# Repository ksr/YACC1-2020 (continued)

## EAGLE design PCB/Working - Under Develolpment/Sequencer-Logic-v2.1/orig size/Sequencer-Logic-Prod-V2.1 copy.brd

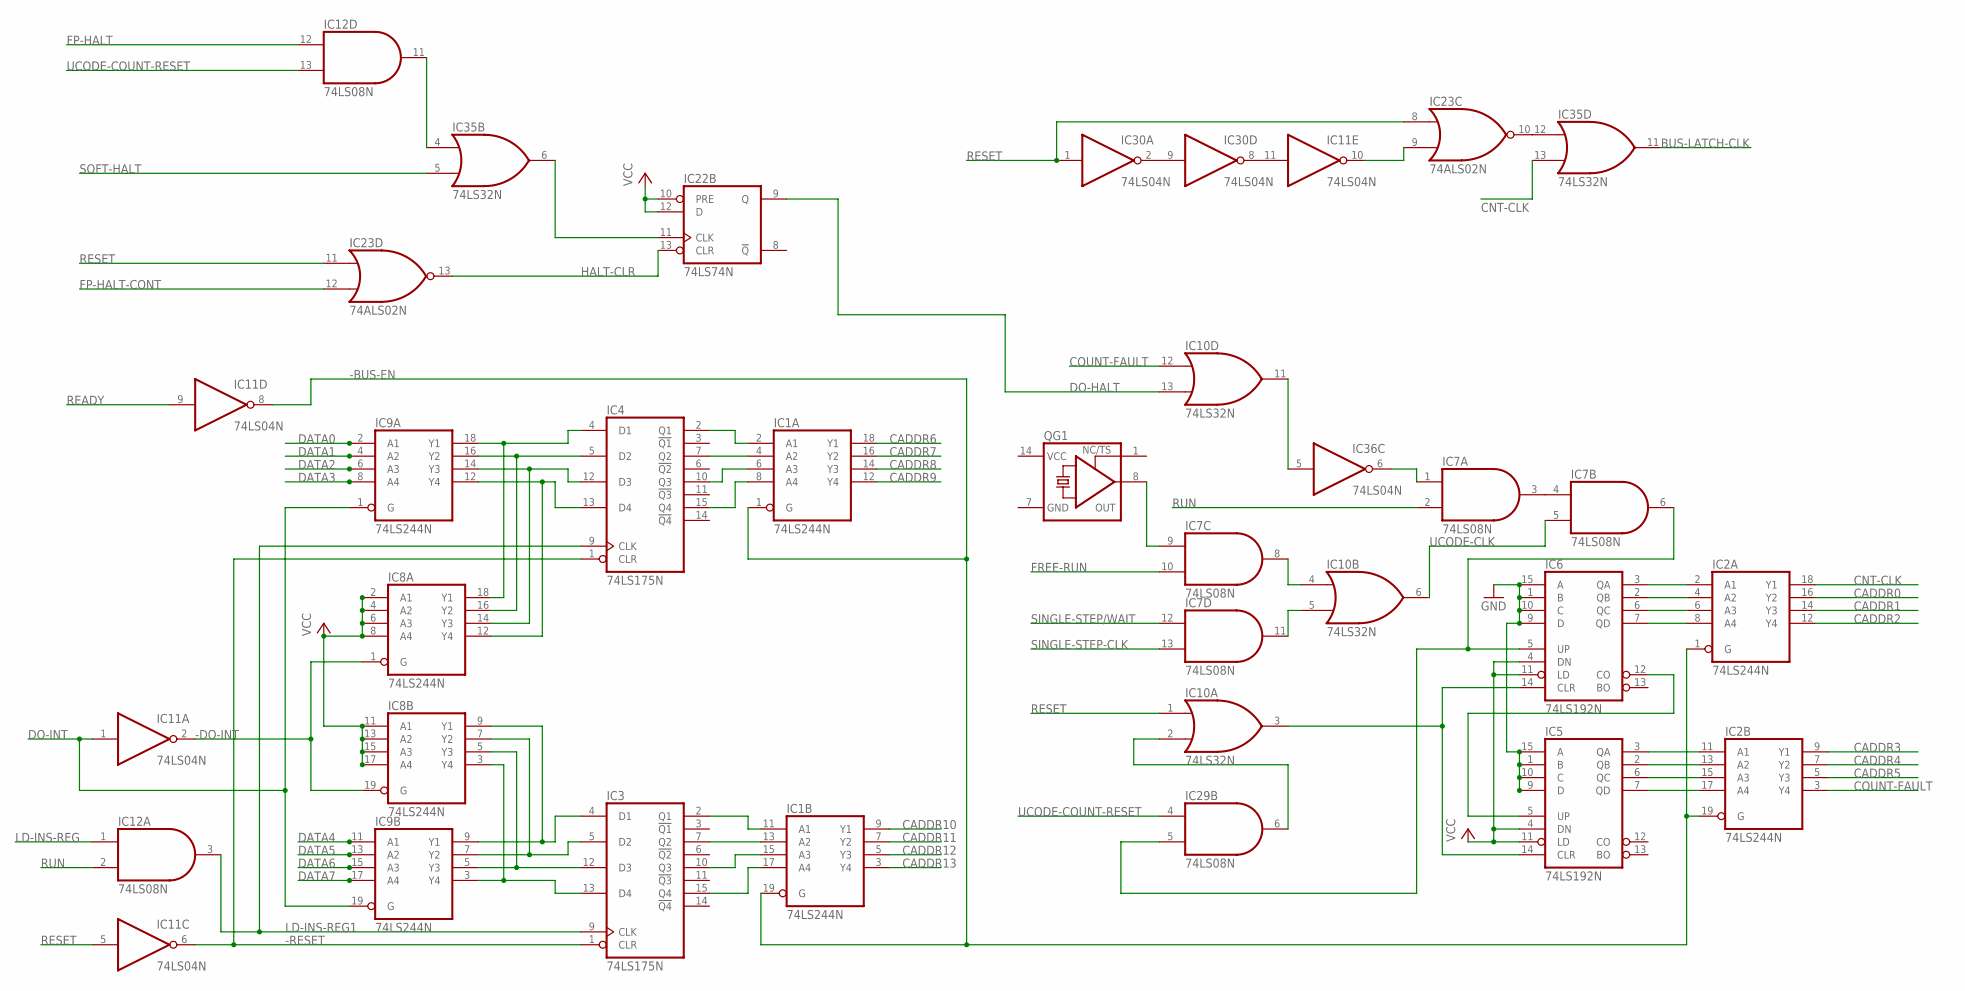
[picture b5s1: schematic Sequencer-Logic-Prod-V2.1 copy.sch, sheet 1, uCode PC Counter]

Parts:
IC1, IC2, IC8, IC9: 74LS244N; DIL20
IC3, IC4: 74LS175N; DIL16
IC5, IC6: 74LS192N; DIL16
IC7, IC12, IC29: 74LS08N; DIL14
IC10, IC35: 74LS32N; DIL14
IC11, IC30, IC36: 74LS04N; DIL14
IC22: 74LS74N; DIL14
IC23: 74ALS02N; DIL14
QG1: XO-14; DIL14S

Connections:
-BUS-EN: IC1.1 (G), IC1.19 (G), IC2.1 (G), IC2.19 (G), IC11.8 (O); also elsewhere on the board
-DO-INT: IC8.1 (G), IC8.19 (G), IC11.2 (O)
-RESET: IC3.1 (CLR), IC4.1 (CLR), IC11.6 (O); also elsewhere on the board
BUS-LATCH-CLK: IC35.11 (O); also elsewhere on the board
CADDR0: IC2.16 (Y2); also elsewhere on the board
CADDR1: IC2.14 (Y3); also elsewhere on the board
CADDR2: IC2.12 (Y4); also elsewhere on the board
CADDR3: IC2.9 (Y1); also elsewhere on the board
CADDR4: IC2.7 (Y2); also elsewhere on the board
CADDR5: IC2.5 (Y3); also elsewhere on the board
CADDR6: IC1.18 (Y1); also elsewhere on the board
CADDR7: IC1.16 (Y2); also elsewhere on the board
CADDR8: IC1.14 (Y3); also elsewhere on the board
CADDR9: IC1.12 (Y4); also elsewhere on the board
CADDR10: IC1.9 (Y1); also elsewhere on the board
CADDR11: IC1.7 (Y2); also elsewhere on the board
CADDR12: IC1.5 (Y3); also elsewhere on the board
CADDR13: IC1.3 (Y4); also elsewhere on the board
CNT-CLK: IC2.18 (Y1), IC35.13 (I1)
COUNT-FAULT: IC2.3 (Y4), IC10.12 (I0)
COUNT-RESET: IC5.14 (CLR), IC6.14 (CLR), IC10.3 (O)
DATA0: IC9.2 (A1); also elsewhere on the board
DATA1: IC9.4 (A2); also elsewhere on the board
DATA2: IC9.6 (A3); also elsewhere on the board
DATA3: IC9.8 (A4); also elsewhere on the board
DATA4: IC9.11 (A1); also elsewhere on the board
DATA5: IC9.13 (A2); also elsewhere on the board
DATA6: IC9.15 (A3); also elsewhere on the board
DATA7: IC9.17 (A4); also elsewhere on the board
DO-HALT: IC10.13 (I1), IC22.9 (Q)
DO-INT: IC9.1 (G), IC9.19 (G), IC11.1 (I); also elsewhere on the board
FP-HALT: IC12.12 (I0); also elsewhere on the board
FP-HALT-CONT: IC23.12 (I1); also elsewhere on the board
FREE-RUN: IC7.10 (I1); also elsewhere on the board
GND: IC1.10 (GND), IC2.10 (GND), IC3.8 (GND), IC4.8 (GND), IC5.1 (B), IC5.8 (GND), IC5.9 (D), IC5.10 (C), IC5.15 (A), IC6.1 (B), IC6.8 (GND), IC6.9 (D), IC6.10 (C), IC6.15 (A), IC7.7 (GND), IC8.10 (GND), IC9.10 (GND), IC10.7 (GND), IC11.7 (GND), IC12.7 (GND), IC22.7 (GND), IC23.7 (GND), IC29.7 (GND), IC30.7 (GND), IC35.7 (GND), IC36.7 (GND), QG1.7 (GND); also elsewhere on the board
HALT-CLR: IC22.13 (CLR), IC23.13 (O)
LD-INS-REG: IC12.1 (I0); also elsewhere on the board
LD-INS-REG1: IC3.9 (CLK), IC4.9 (CLK), IC12.3 (O)
unnamed: IC5.5 (UP), IC6.12 (CO)
unnamed: IC1.2 (A1), IC4.2 (Q1)
unnamed: IC1.4 (A2), IC4.7 (Q2)
unnamed: IC6.5 (UP), IC7.6 (O), IC29.5 (I1)
unnamed: IC4.4 (D1), IC8.18 (Y1), IC9.18 (Y1)
unnamed: IC4.5 (D2), IC8.16 (Y2), IC9.16 (Y2)
unnamed: IC2.2 (A1), IC6.3 (QA)
unnamed: IC2.4 (A2), IC6.2 (QB)
unnamed: IC2.6 (A3), IC6.6 (QC)
unnamed: IC1.6 (A3), IC4.10 (Q3)
unnamed: IC2.8 (A4), IC6.7 (QD)
unnamed: IC2.11 (A1), IC5.3 (QA)
unnamed: IC2.13 (A2), IC5.2 (QB)
unnamed: IC2.15 (A3), IC5.6 (QC)
unnamed: IC2.17 (A4), IC5.7 (QD)
unnamed: IC7.1 (I0), IC36.6 (O)
unnamed: IC4.12 (D3), IC8.14 (Y3), IC9.14 (Y3)
unnamed: IC4.13 (D4), IC8.12 (Y4), IC9.12 (Y4)
unnamed: IC3.4 (D1), IC8.9 (Y1), IC9.9 (Y1)
unnamed: IC3.5 (D2), IC8.7 (Y2), IC9.7 (Y2)
unnamed: IC3.12 (D3), IC8.5 (Y3), IC9.5 (Y3)
unnamed: IC3.13 (D4), IC8.3 (Y4), IC9.3 (Y4)
unnamed: IC1.8 (A4), IC4.15 (Q4)
unnamed: IC10.11 (O), IC36.5 (I)
unnamed: IC7.3 (O), IC7.4 (I0)
unnamed: IC23.10 (O), IC35.12 (I0)
unnamed: IC22.11 (CLK), IC35.6 (O)
unnamed: IC1.11 (A1), IC3.2 (Q1)
unnamed: IC1.13 (A2), IC3.7 (Q2)
unnamed: IC1.15 (A3), IC3.10 (Q3)
unnamed: IC1.17 (A4), IC3.15 (Q4)
unnamed: IC7.11 (O), IC10.5 (I1)
unnamed: IC7.8 (O), IC10.4 (I0)
unnamed: IC7.9 (I0), QG1.8 (OUT)
unnamed: IC11.11 (I), IC30.8 (O)
unnamed: IC30.2 (O), IC30.9 (I)
unnamed: IC11.10 (O), IC23.9 (I1)
unnamed: IC12.11 (O), IC35.4 (I0)
unnamed: IC10.2 (I1), IC29.6 (O)
READY: IC11.9 (I); also elsewhere on the board
RESET: IC10.1 (I0), IC11.5 (I), IC23.8 (I0), IC23.11 (I0), IC30.1 (I); also elsewhere on the board
RUN: IC7.2 (I1), IC12.2 (I1); also elsewhere on the board
SINGLE-STEP-CLK: IC7.13 (I1); also elsewhere on the board
SINGLE-STEP/WAIT: IC7.12 (I0); also elsewhere on the board
SOFT-HALT: IC35.5 (I1); also elsewhere on the board
UCODE-CLK: IC7.5 (I1), IC10.6 (O)
UCODE-COUNT-RESET: IC12.13 (I1), IC29.4 (I0); also elsewhere on the board
VCC: IC1.20 (VCC), IC2.20 (VCC), IC3.16 (VCC), IC4.16 (VCC), IC5.4 (DN), IC5.11 (LD), IC5.16 (VCC), IC6.4 (DN), IC6.11 (LD), IC6.16 (VCC), IC7.14 (VCC), IC8.2 (A1), IC8.4 (A2), IC8.6 (A3), IC8.8 (A4), IC8.11 (A1), IC8.13 (A2), IC8.15 (A3), IC8.17 (A4), IC8.20 (VCC), IC9.20 (VCC), IC10.14 (VCC), IC11.14 (VCC), IC12.14 (VCC), IC22.10 (PRE), IC22.12 (D), IC22.14 (VCC), IC23.14 (VCC), IC29.14 (VCC), IC30.14 (VCC), IC35.14 (VCC), IC36.14 (VCC), QG1.14 (VCC); also elsewhere on the board

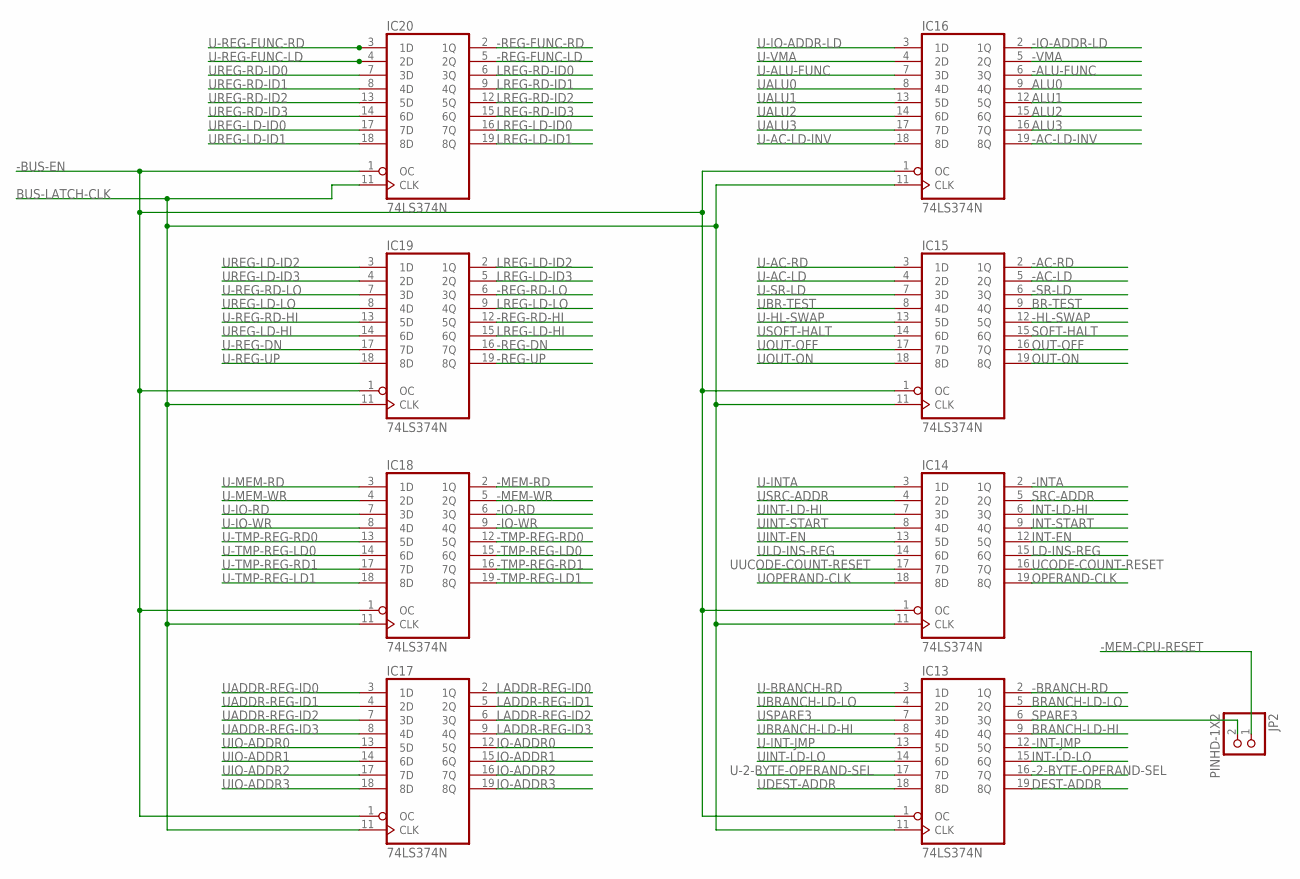
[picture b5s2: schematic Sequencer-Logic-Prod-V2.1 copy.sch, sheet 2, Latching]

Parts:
IC13, IC14, IC15, IC16, IC17, IC18, IC19, IC20: 74LS374N; DIL20
JP2: PINHD-1X2; 1X02

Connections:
-2-BYTE-OPERAND-SEL: IC13.16 (7Q); also elsewhere on the board
-AC-LD: IC15.5 (2Q); also elsewhere on the board
-AC-LD-INV: IC16.19 (8Q); also elsewhere on the board
-AC-RD: IC15.2 (1Q); also elsewhere on the board
-ALU-FUNC: IC16.6 (3Q); also elsewhere on the board
-BRANCH-RD: IC13.2 (1Q); also elsewhere on the board
-BUS-EN: IC13.1 (OC), IC14.1 (OC), IC15.1 (OC), IC16.1 (OC), IC17.1 (OC), IC18.1 (OC), IC19.1 (OC), IC20.1 (OC); also elsewhere on the board
-HL-SWAP: IC15.12 (5Q); also elsewhere on the board
-INT-JMP: IC13.12 (5Q); also elsewhere on the board
-INTA: IC14.2 (1Q); also elsewhere on the board
-IO-ADDR-LD: IC16.2 (1Q); also elsewhere on the board
-IO-RD: IC18.6 (3Q); also elsewhere on the board
-IO-WR: IC18.9 (4Q); also elsewhere on the board
-MEM-CPU-RESET: JP2.1; also elsewhere on the board
-MEM-RD: IC18.2 (1Q); also elsewhere on the board
-MEM-WR: IC18.5 (2Q); also elsewhere on the board
-REG-DN: IC19.16 (7Q); also elsewhere on the board
-REG-FUNC-LD: IC20.5 (2Q); also elsewhere on the board
-REG-FUNC-RD: IC20.2 (1Q); also elsewhere on the board
-REG-RD-HI: IC19.12 (5Q); also elsewhere on the board
-REG-RD-LO: IC19.6 (3Q); also elsewhere on the board
-REG-UP: IC19.19 (8Q); also elsewhere on the board
-SR-LD: IC15.6 (3Q); also elsewhere on the board
-TMP-REG-LD0: IC18.15 (6Q); also elsewhere on the board
-TMP-REG-LD1: IC18.19 (8Q); also elsewhere on the board
-TMP-REG-RD0: IC18.12 (5Q); also elsewhere on the board
-TMP-REG-RD1: IC18.16 (7Q); also elsewhere on the board
-VMA: IC16.5 (2Q); also elsewhere on the board
ALU0: IC16.9 (4Q); also elsewhere on the board
ALU1: IC16.12 (5Q); also elsewhere on the board
ALU2: IC16.15 (6Q); also elsewhere on the board
ALU3: IC16.16 (7Q); also elsewhere on the board
BR-TEST: IC15.9 (4Q); also elsewhere on the board
BRANCH-LD-HI: IC13.9 (4Q); also elsewhere on the board
BRANCH-LD-LO: IC13.5 (2Q); also elsewhere on the board
BUS-LATCH-CLK: IC13.11 (CLK), IC14.11 (CLK), IC15.11 (CLK), IC16.11 (CLK), IC17.11 (CLK), IC18.11 (CLK), IC19.11 (CLK), IC20.11 (CLK); also elsewhere on the board
DEST-ADDR: IC13.19 (8Q); also elsewhere on the board
GND: IC13.10 (GND), IC14.10 (GND), IC15.10 (GND), IC16.10 (GND), IC17.10 (GND), IC18.10 (GND), IC19.10 (GND), IC20.10 (GND); also elsewhere on the board
INT-EN: IC14.12 (5Q); also elsewhere on the board
INT-LD-HI: IC14.6 (3Q); also elsewhere on the board
INT-LD-LO: IC13.15 (6Q); also elsewhere on the board
INT-START: IC14.9 (4Q); also elsewhere on the board
IO-ADDR0: IC17.12 (5Q); also elsewhere on the board
IO-ADDR1: IC17.15 (6Q); also elsewhere on the board
IO-ADDR2: IC17.16 (7Q); also elsewhere on the board
IO-ADDR3: IC17.19 (8Q); also elsewhere on the board
LADDR-REG-ID0: IC17.2 (1Q); also elsewhere on the board
LADDR-REG-ID1: IC17.5 (2Q); also elsewhere on the board
LADDR-REG-ID2: IC17.6 (3Q); also elsewhere on the board
LADDR-REG-ID3: IC17.9 (4Q); also elsewhere on the board
LD-INS-REG: IC14.15 (6Q); also elsewhere on the board
LREG-LD-HI: IC19.15 (6Q); also elsewhere on the board
LREG-LD-ID0: IC20.16 (7Q); also elsewhere on the board
LREG-LD-ID1: IC20.19 (8Q); also elsewhere on the board
LREG-LD-ID2: IC19.2 (1Q); also elsewhere on the board
LREG-LD-ID3: IC19.5 (2Q); also elsewhere on the board
LREG-LD-LO: IC19.9 (4Q); also elsewhere on the board
LREG-RD-ID0: IC20.6 (3Q); also elsewhere on the board
LREG-RD-ID1: IC20.9 (4Q); also elsewhere on the board
LREG-RD-ID2: IC20.12 (5Q); also elsewhere on the board
LREG-RD-ID3: IC20.15 (6Q); also elsewhere on the board
OPERAND-CLK: IC14.19 (8Q); also elsewhere on the board
OUT-OFF: IC15.16 (7Q); also elsewhere on the board
OUT-ON: IC15.19 (8Q); also elsewhere on the board
SOFT-HALT: IC15.15 (6Q); also elsewhere on the board
SPARE3: IC13.6 (3Q), JP2.2
SRC-ADDR: IC14.5 (2Q); also elsewhere on the board
U-2-BYTE-OPERAND-SEL: IC13.17 (7D); also elsewhere on the board
U-AC-LD: IC15.4 (2D); also elsewhere on the board
U-AC-LD-INV: IC16.18 (8D); also elsewhere on the board
U-AC-RD: IC15.3 (1D); also elsewhere on the board
U-ALU-FUNC: IC16.7 (3D); also elsewhere on the board
U-BRANCH-RD: IC13.3 (1D); also elsewhere on the board
U-HL-SWAP: IC15.13 (5D); also elsewhere on the board
U-INT-JMP: IC13.13 (5D); also elsewhere on the board
U-INTA: IC14.3 (1D); also elsewhere on the board
U-IO-ADDR-LD: IC16.3 (1D); also elsewhere on the board
U-IO-RD: IC18.7 (3D); also elsewhere on the board
U-IO-WR: IC18.8 (4D); also elsewhere on the board
U-MEM-RD: IC18.3 (1D); also elsewhere on the board
U-MEM-WR: IC18.4 (2D); also elsewhere on the board
U-REG-DN: IC19.17 (7D); also elsewhere on the board
U-REG-FUNC-LD: IC20.4 (2D); also elsewhere on the board
U-REG-FUNC-RD: IC20.3 (1D); also elsewhere on the board
U-REG-RD-HI: IC19.13 (5D); also elsewhere on the board
U-REG-RD-LO: IC19.7 (3D); also elsewhere on the board
U-REG-UP: IC19.18 (8D); also elsewhere on the board
U-SR-LD: IC15.7 (3D); also elsewhere on the board
U-TMP-REG-LD0: IC18.14 (6D); also elsewhere on the board
U-TMP-REG-LD1: IC18.18 (8D); also elsewhere on the board
U-TMP-REG-RD0: IC18.13 (5D); also elsewhere on the board
U-TMP-REG-RD1: IC18.17 (7D); also elsewhere on the board
U-VMA: IC16.4 (2D); also elsewhere on the board
UADDR-REG-ID0: IC17.3 (1D); also elsewhere on the board
UADDR-REG-ID1: IC17.4 (2D); also elsewhere on the board
UADDR-REG-ID2: IC17.7 (3D); also elsewhere on the board
UADDR-REG-ID3: IC17.8 (4D); also elsewhere on the board
UALU0: IC16.8 (4D); also elsewhere on the board
UALU1: IC16.13 (5D); also elsewhere on the board
UALU2: IC16.14 (6D); also elsewhere on the board
UALU3: IC16.17 (7D); also elsewhere on the board
UBR-TEST: IC15.8 (4D); also elsewhere on the board
UBRANCH-LD-HI: IC13.8 (4D); also elsewhere on the board
UBRANCH-LD-LO: IC13.4 (2D); also elsewhere on the board
UCODE-COUNT-RESET: IC14.16 (7Q); also elsewhere on the board
UDEST-ADDR: IC13.18 (8D); also elsewhere on the board
UINT-EN: IC14.13 (5D); also elsewhere on the board
UINT-LD-HI: IC14.7 (3D); also elsewhere on the board
UINT-LD-LO: IC13.14 (6D); also elsewhere on the board
UINT-START: IC14.8 (4D); also elsewhere on the board
UIO-ADDR0: IC17.13 (5D); also elsewhere on the board
UIO-ADDR1: IC17.14 (6D); also elsewhere on the board
UIO-ADDR2: IC17.17 (7D); also elsewhere on the board
UIO-ADDR3: IC17.18 (8D); also elsewhere on the board
ULD-INS-REG: IC14.14 (6D); also elsewhere on the board
UOPERAND-CLK: IC14.18 (8D); also elsewhere on the board
UOUT-OFF: IC15.17 (7D); also elsewhere on the board
UOUT-ON: IC15.18 (8D); also elsewhere on the board
UREG-LD-HI: IC19.14 (6D); also elsewhere on the board
UREG-LD-ID0: IC20.17 (7D); also elsewhere on the board
UREG-LD-ID1: IC20.18 (8D); also elsewhere on the board
UREG-LD-ID2: IC19.3 (1D); also elsewhere on the board
UREG-LD-ID3: IC19.4 (2D); also elsewhere on the board
UREG-LD-LO: IC19.8 (4D); also elsewhere on the board
UREG-RD-ID0: IC20.7 (3D); also elsewhere on the board
UREG-RD-ID1: IC20.8 (4D); also elsewhere on the board
UREG-RD-ID2: IC20.13 (5D); also elsewhere on the board
UREG-RD-ID3: IC20.14 (6D); also elsewhere on the board
USOFT-HALT: IC15.14 (6D); also elsewhere on the board
USPARE3: IC13.7 (3D); also elsewhere on the board
USRC-ADDR: IC14.4 (2D); also elsewhere on the board
UUCODE-COUNT-RESET: IC14.17 (7D); also elsewhere on the board
VCC: IC13.20 (VCC), IC14.20 (VCC), IC15.20 (VCC), IC16.20 (VCC), IC17.20 (VCC), IC18.20 (VCC), IC19.20 (VCC), IC20.20 (VCC); also elsewhere on the board

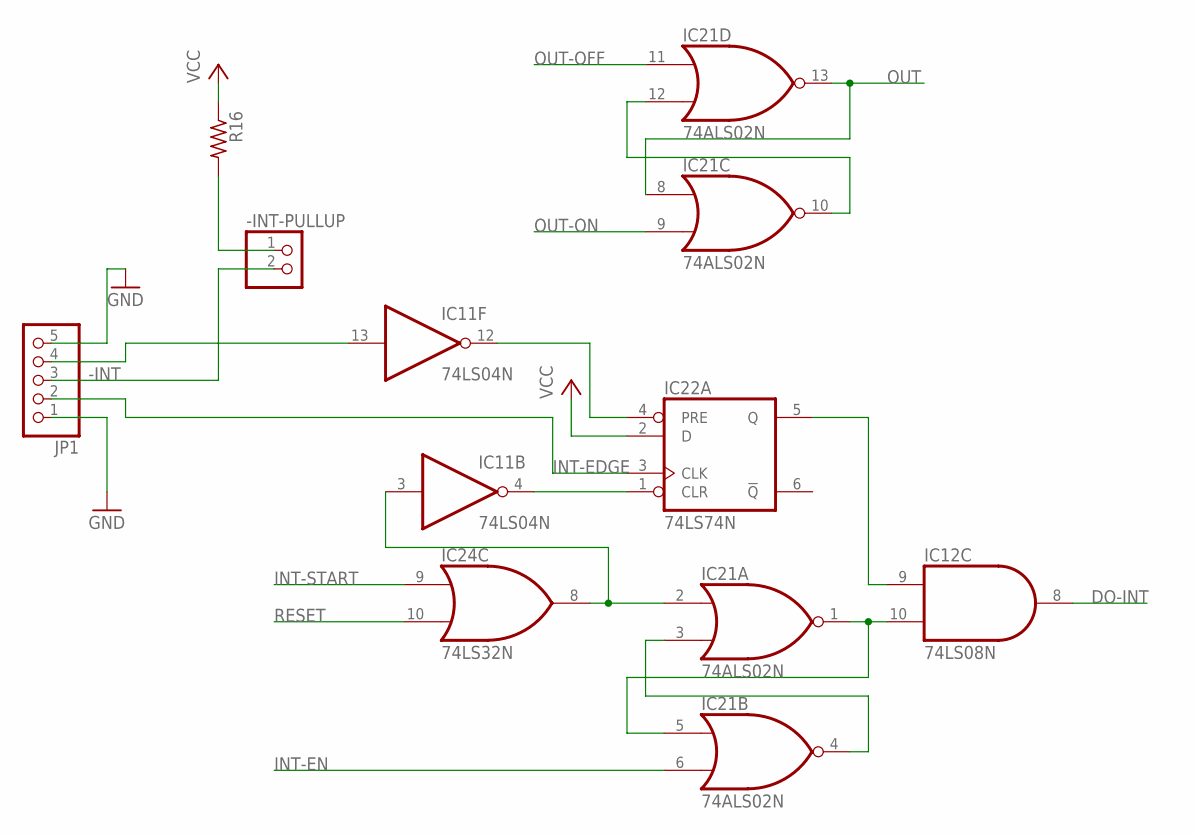
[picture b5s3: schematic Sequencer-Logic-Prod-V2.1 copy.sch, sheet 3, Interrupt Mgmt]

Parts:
-INT-PULLUP: PINHD-1X2; 1X02
IC11: 74LS04N; DIL14
IC12: 74LS08N; DIL14
IC21: 74ALS02N; DIL14
IC22: 74LS74N; DIL14
IC24: 74LS32N; DIL14
JP1: PINHD-1X5; 1X05
R16: 10k; 0207/10

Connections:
-INT: -INT-PULLUP.2, JP1.3; also elsewhere on the board
DO-INT: IC12.8 (O); also elsewhere on the board
GND: IC11.7 (GND), IC12.7 (GND), IC21.7 (GND), IC22.7 (GND), IC24.7 (GND), JP1.1, JP1.5; also elsewhere on the board
INT-EDGE: IC22.3 (CLK), JP1.2
INT-EN: IC21.6 (I1); also elsewhere on the board
INT-START: IC24.9 (I0); also elsewhere on the board
unnamed: IC12.10 (I1), IC21.1 (O), IC21.5 (I0)
unnamed: IC21.3 (I1), IC21.4 (O)
unnamed: IC11.3 (I), IC21.2 (I0), IC24.8 (O)
unnamed: IC12.9 (I0), IC22.5 (Q)
unnamed: IC11.4 (O), IC22.1 (CLR)
unnamed: IC11.12 (O), IC22.4 (PRE)
unnamed: IC11.13 (I), JP1.4
unnamed: IC21.10 (O), IC21.12 (I1)
unnamed: -INT-PULLUP.1, R16.2
OUT: IC21.8 (I0), IC21.13 (O); also elsewhere on the board
OUT-OFF: IC21.11 (I0); also elsewhere on the board
OUT-ON: IC21.9 (I1); also elsewhere on the board
RESET: IC24.10 (I1); also elsewhere on the board
VCC: IC11.14 (VCC), IC12.14 (VCC), IC21.14 (VCC), IC22.2 (D), IC22.14 (VCC), IC24.14 (VCC), R16.1; also elsewhere on the board

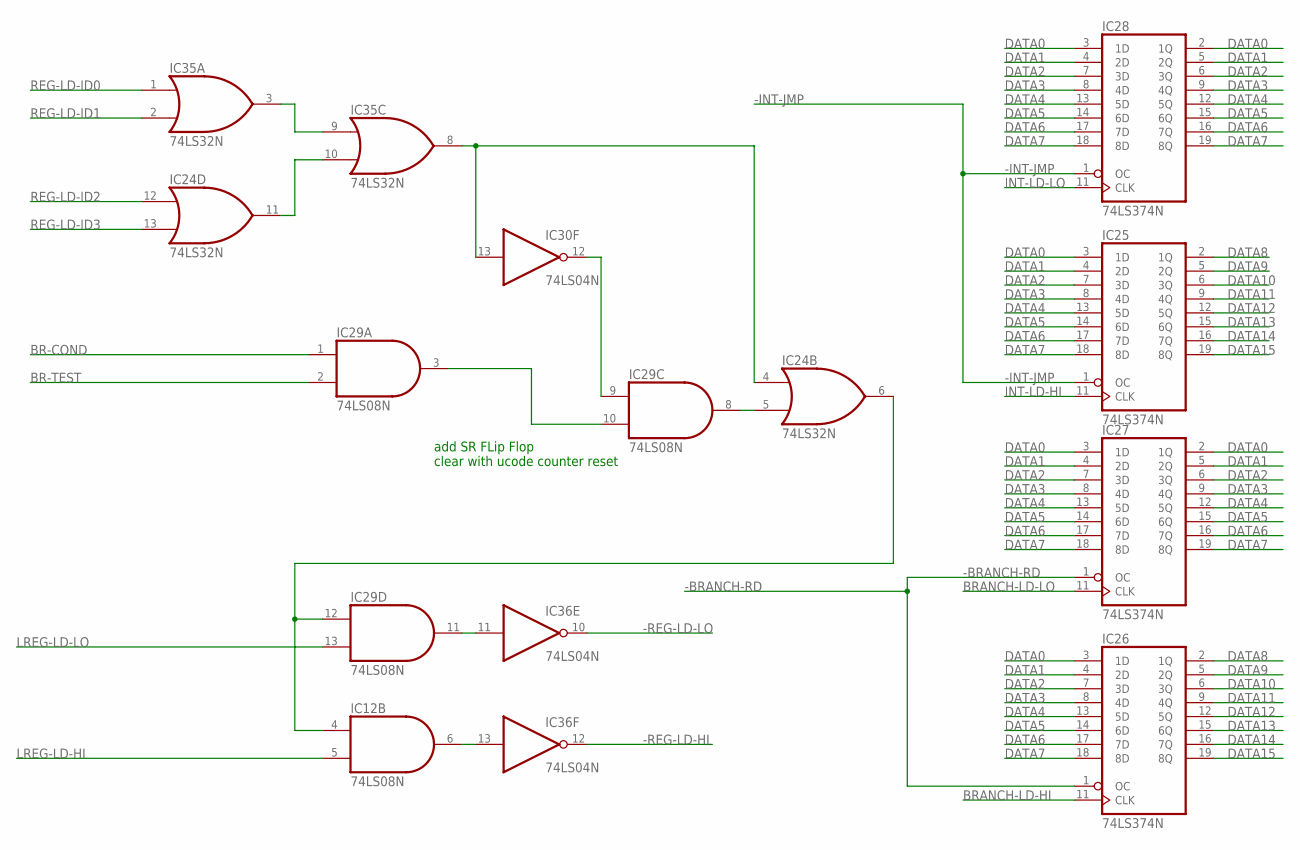
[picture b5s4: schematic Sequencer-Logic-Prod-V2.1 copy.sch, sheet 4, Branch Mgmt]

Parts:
IC12, IC29: 74LS08N; DIL14
IC24, IC35: 74LS32N; DIL14
IC25, IC26, IC27, IC28: 74LS374N; DIL20
IC30, IC36: 74LS04N; DIL14

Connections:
-BRANCH-RD: IC26.1 (OC), IC27.1 (OC); also elsewhere on the board
-INT-JMP: IC25.1 (OC), IC28.1 (OC); also elsewhere on the board
-REG-LD-HI: IC36.12 (O); also elsewhere on the board
-REG-LD-LO: IC36.10 (O); also elsewhere on the board
BR-COND: IC29.1 (I0); also elsewhere on the board
BR-TEST: IC29.2 (I1); also elsewhere on the board
BRANCH-LD-HI: IC26.11 (CLK); also elsewhere on the board
BRANCH-LD-LO: IC27.11 (CLK); also elsewhere on the board
DATA0: IC25.3 (1D), IC26.3 (1D), IC27.2 (1Q), IC27.3 (1D), IC28.2 (1Q), IC28.3 (1D); also elsewhere on the board
DATA1: IC25.4 (2D), IC26.4 (2D), IC27.4 (2D), IC27.5 (2Q), IC28.4 (2D), IC28.5 (2Q); also elsewhere on the board
DATA2: IC25.7 (3D), IC26.7 (3D), IC27.6 (3Q), IC27.7 (3D), IC28.6 (3Q), IC28.7 (3D); also elsewhere on the board
DATA3: IC25.8 (4D), IC26.8 (4D), IC27.8 (4D), IC27.9 (4Q), IC28.8 (4D), IC28.9 (4Q); also elsewhere on the board
DATA4: IC25.13 (5D), IC26.13 (5D), IC27.12 (5Q), IC27.13 (5D), IC28.12 (5Q), IC28.13 (5D); also elsewhere on the board
DATA5: IC25.14 (6D), IC26.14 (6D), IC27.14 (6D), IC27.15 (6Q), IC28.14 (6D), IC28.15 (6Q); also elsewhere on the board
DATA6: IC25.17 (7D), IC26.17 (7D), IC27.16 (7Q), IC27.17 (7D), IC28.16 (7Q), IC28.17 (7D); also elsewhere on the board
DATA7: IC25.18 (8D), IC26.18 (8D), IC27.18 (8D), IC27.19 (8Q), IC28.18 (8D), IC28.19 (8Q); also elsewhere on the board
DATA8: IC25.2 (1Q), IC26.2 (1Q); also elsewhere on the board
DATA9: IC25.5 (2Q), IC26.5 (2Q); also elsewhere on the board
DATA10: IC25.6 (3Q), IC26.6 (3Q); also elsewhere on the board
DATA11: IC25.9 (4Q), IC26.9 (4Q); also elsewhere on the board
DATA12: IC25.12 (5Q), IC26.12 (5Q); also elsewhere on the board
DATA13: IC25.15 (6Q), IC26.15 (6Q); also elsewhere on the board
DATA14: IC25.16 (7Q), IC26.16 (7Q); also elsewhere on the board
DATA15: IC25.19 (8Q), IC26.19 (8Q); also elsewhere on the board
GND: IC12.7 (GND), IC24.7 (GND), IC25.10 (GND), IC26.10 (GND), IC27.10 (GND), IC28.10 (GND), IC29.7 (GND), IC30.7 (GND), IC35.7 (GND), IC36.7 (GND); also elsewhere on the board
INT-LD-HI: IC25.11 (CLK); also elsewhere on the board
INT-LD-LO: IC28.11 (CLK); also elsewhere on the board
LREG-LD-HI: IC12.5 (I1); also elsewhere on the board
LREG-LD-LO: IC29.13 (I1); also elsewhere on the board
unnamed: IC35.3 (O), IC35.9 (I0)
unnamed: IC24.11 (O), IC35.10 (I1)
unnamed: IC29.3 (O), IC29.10 (I1)
unnamed: IC29.9 (I0), IC30.12 (O)
unnamed: IC24.5 (I1), IC29.8 (O)
unnamed: IC12.4 (I0), IC24.6 (O), IC29.12 (I0)
unnamed: IC24.4 (I0), IC30.13 (I), IC35.8 (O)
unnamed: IC29.11 (O), IC36.11 (I)
unnamed: IC12.6 (O), IC36.13 (I)
REG-LD-ID0: IC35.1 (I0); also elsewhere on the board
REG-LD-ID1: IC35.2 (I1); also elsewhere on the board
REG-LD-ID2: IC24.12 (I0); also elsewhere on the board
REG-LD-ID3: IC24.13 (I1); also elsewhere on the board
VCC: IC12.14 (VCC), IC24.14 (VCC), IC25.20 (VCC), IC26.20 (VCC), IC27.20 (VCC), IC28.20 (VCC), IC29.14 (VCC), IC30.14 (VCC), IC35.14 (VCC), IC36.14 (VCC); also elsewhere on the board

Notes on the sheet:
add SR FLip Flop clear with ucode counter reset

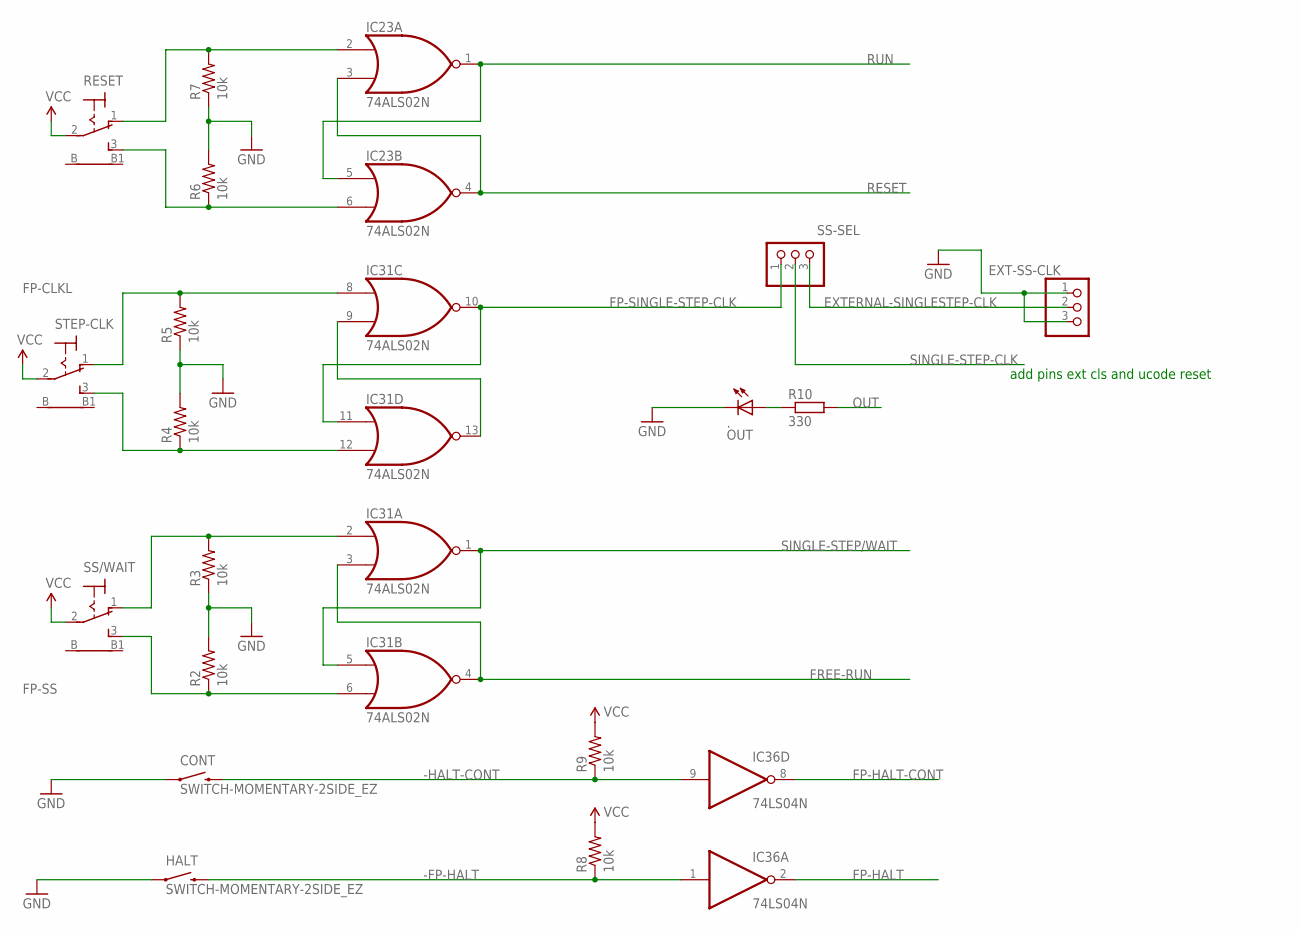
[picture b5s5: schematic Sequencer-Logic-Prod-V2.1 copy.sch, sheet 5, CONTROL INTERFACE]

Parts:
.: OUT; LED5MM
CONT: SWITCH-MOMENTARY-2SIDE_EZ; TACTILE-PTH-SIDEEZ
EXT-SS-CLK: PINHD-1X3; 1X03
HALT: SWITCH-MOMENTARY-2SIDE_EZ; TACTILE-PTH-SIDEEZ
IC23, IC31: 74ALS02N; DIL14
IC36: 74LS04N; DIL14
R2, R3, R4, R5, R6, R7, R8, R9: 10k; 0207/10
R10: 330; 0207/10
RESET: 9070-1W
SS-SEL: PINHD-1X3; 1X03
SS/WAIT: 9070-1W
STEP-CLK: 9070-1W

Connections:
-FP-HALT: HALT.2, IC36.1 (I), R8.1
-HALT-CONT: CONT.2, IC36.9 (I), R9.1
EXTERNAL-SINGLESTEP-CLK: EXT-SS-CLK.2, SS-SEL.3
FP-CLKH: IC31.12 (I1), R4.1, STEP-CLK.3 (S)
FP-CLKL: IC31.8 (I0), R5.2, STEP-CLK.1 (O)
FP-EXECUTE: IC23.6 (I1), R6.1, RESET.3 (S)
FP-FREERUN: IC31.2 (I0), R3.2, SS/WAIT.1 (O)
FP-HALT: IC36.2 (O); also elsewhere on the board
FP-HALT-CONT: IC36.8 (O); also elsewhere on the board
FP-RESET: IC23.2 (I0), R7.2, RESET.1 (O)
FP-SINGLE-STEP-CLK: IC31.10 (O), IC31.11 (I0), SS-SEL.1
FP-SS: IC31.6 (I1), R2.1, SS/WAIT.3 (S)
FREE-RUN: IC31.3 (I1), IC31.4 (O); also elsewhere on the board
GND: ..K (C), CONT.1, EXT-SS-CLK.1, EXT-SS-CLK.3, HALT.1, IC23.7 (GND), IC31.7 (GND), IC36.7 (GND), R2.2, R3.1, R4.2, R5.1, R6.2, R7.1; also elsewhere on the board
HARD-RESET1: IC31.9 (I1), IC31.13 (O)
unnamed: ..A, R10.1
OUT: R10.2; also elsewhere on the board
RESET: IC23.3 (I1), IC23.4 (O); also elsewhere on the board
RUN: IC23.1 (O), IC23.5 (I0); also elsewhere on the board
SINGLE-STEP-CLK: SS-SEL.2; also elsewhere on the board
SINGLE-STEP/WAIT: IC31.1 (O), IC31.5 (I0); also elsewhere on the board
VCC: IC23.14 (VCC), IC31.14 (VCC), IC36.14 (VCC), R8.2, R9.2, RESET.2, SS/WAIT.2, STEP-CLK.2; also elsewhere on the board

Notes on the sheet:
add pins ext cls and ucode reset

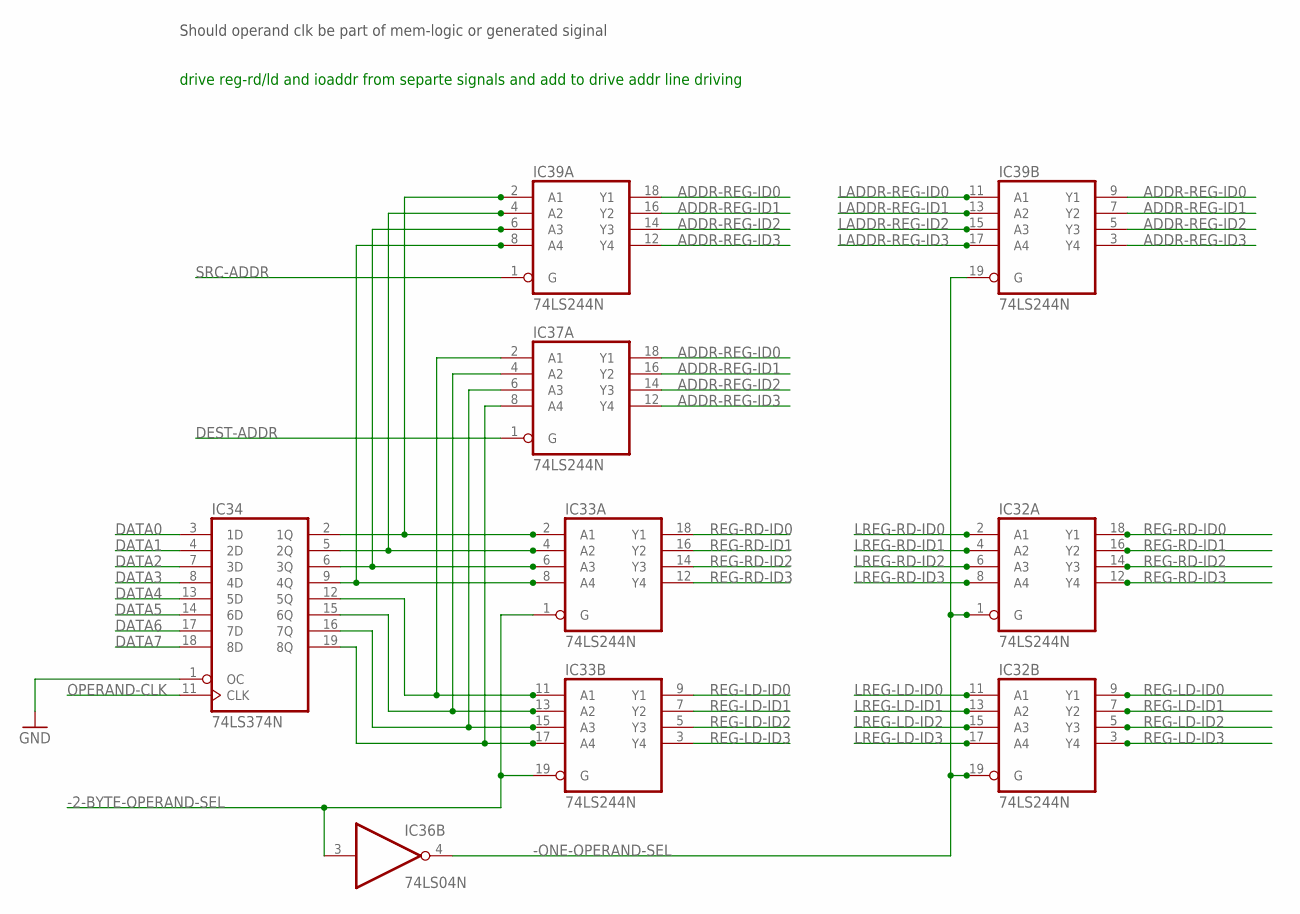
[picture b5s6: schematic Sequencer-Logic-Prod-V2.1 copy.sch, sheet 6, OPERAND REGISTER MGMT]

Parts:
IC32, IC33, IC37, IC39: 74LS244N; DIL20
IC34: 74LS374N; DIL20
IC36: 74LS04N; DIL14

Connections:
-2-BYTE-OPERAND-SEL: IC33.1 (G), IC33.19 (G), IC36.3 (I); also elsewhere on the board
-ONE-OPERAND-SEL: IC32.1 (G), IC32.19 (G), IC36.4 (O), IC39.19 (G)
ADDR-REG-ID0: IC37.18 (Y1), IC39.9 (Y1), IC39.18 (Y1); also elsewhere on the board
ADDR-REG-ID1: IC37.16 (Y2), IC39.7 (Y2), IC39.16 (Y2); also elsewhere on the board
ADDR-REG-ID2: IC37.14 (Y3), IC39.5 (Y3), IC39.14 (Y3); also elsewhere on the board
ADDR-REG-ID3: IC37.12 (Y4), IC39.3 (Y4), IC39.12 (Y4); also elsewhere on the board
DATA0: IC34.3 (1D); also elsewhere on the board
DATA1: IC34.4 (2D); also elsewhere on the board
DATA2: IC34.7 (3D); also elsewhere on the board
DATA3: IC34.8 (4D); also elsewhere on the board
DATA4: IC34.13 (5D); also elsewhere on the board
DATA5: IC34.14 (6D); also elsewhere on the board
DATA6: IC34.17 (7D); also elsewhere on the board
DATA7: IC34.18 (8D); also elsewhere on the board
DEST-ADDR: IC37.1 (G); also elsewhere on the board
GND: IC32.10 (GND), IC33.10 (GND), IC34.1 (OC), IC34.10 (GND), IC36.7 (GND), IC37.10 (GND), IC39.10 (GND); also elsewhere on the board
LADDR-REG-ID0: IC39.11 (A1); also elsewhere on the board
LADDR-REG-ID1: IC39.13 (A2); also elsewhere on the board
LADDR-REG-ID2: IC39.15 (A3); also elsewhere on the board
LADDR-REG-ID3: IC39.17 (A4); also elsewhere on the board
LREG-LD-ID0: IC32.11 (A1); also elsewhere on the board
LREG-LD-ID1: IC32.13 (A2); also elsewhere on the board
LREG-LD-ID2: IC32.15 (A3); also elsewhere on the board
LREG-LD-ID3: IC32.17 (A4); also elsewhere on the board
LREG-RD-ID0: IC32.2 (A1); also elsewhere on the board
LREG-RD-ID1: IC32.4 (A2); also elsewhere on the board
LREG-RD-ID2: IC32.6 (A3); also elsewhere on the board
LREG-RD-ID3: IC32.8 (A4); also elsewhere on the board
unnamed: IC33.17 (A4), IC34.19 (8Q), IC37.8 (A4)
unnamed: IC33.2 (A1), IC34.2 (1Q), IC39.2 (A1)
unnamed: IC33.4 (A2), IC34.5 (2Q), IC39.4 (A2)
unnamed: IC33.6 (A3), IC34.6 (3Q), IC39.6 (A3)
unnamed: IC33.8 (A4), IC34.9 (4Q), IC39.8 (A4)
unnamed: IC33.11 (A1), IC34.12 (5Q), IC37.2 (A1)
unnamed: IC33.13 (A2), IC34.15 (6Q), IC37.4 (A2)
unnamed: IC33.15 (A3), IC34.16 (7Q), IC37.6 (A3)
OPERAND-CLK: IC34.11 (CLK); also elsewhere on the board
REG-LD-ID0: IC32.9 (Y1), IC33.9 (Y1); also elsewhere on the board
REG-LD-ID1: IC32.7 (Y2), IC33.7 (Y2); also elsewhere on the board
REG-LD-ID2: IC32.5 (Y3), IC33.5 (Y3); also elsewhere on the board
REG-LD-ID3: IC32.3 (Y4), IC33.3 (Y4); also elsewhere on the board
REG-RD-ID0: IC32.18 (Y1), IC33.18 (Y1); also elsewhere on the board
REG-RD-ID1: IC32.16 (Y2), IC33.16 (Y2); also elsewhere on the board
REG-RD-ID2: IC32.14 (Y3), IC33.14 (Y3); also elsewhere on the board
REG-RD-ID3: IC32.12 (Y4), IC33.12 (Y4); also elsewhere on the board
SRC-ADDR: IC39.1 (G); also elsewhere on the board
VCC: IC32.20 (VCC), IC33.20 (VCC), IC34.20 (VCC), IC36.14 (VCC), IC37.20 (VCC), IC39.20 (VCC); also elsewhere on the board

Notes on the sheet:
Should operand clk be part of mem-logic or generated siginal
drive reg-rd/ld and ioaddr from separte signals and add to drive addr line driving

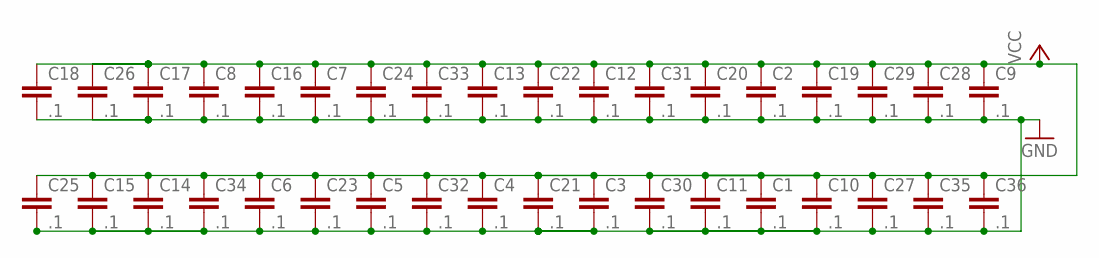
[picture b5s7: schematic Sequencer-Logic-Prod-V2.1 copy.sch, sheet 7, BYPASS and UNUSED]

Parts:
C1, C2, C3, C4, C5, C6, C7, C8, C9, C10, C11, C12, C13, C14, C15, C16, C17, C18, C19, C20, C21, C22, C23, C24, C25, C26, C27, C28, C29, C30, C31, C32, C33, C34, C35, C36: .1; CAP-PTH-SMALLEZ

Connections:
GND: C1.2, C2.2, C3.2, C4.2, C5.2, C6.2, C7.2, C8.2, C9.2, C10.2, C11.2, C12.2, C13.2, C14.2, C15.2, C16.2, C17.2, C18.2, C19.2, C20.2, C21.2, C22.2, C23.2, C24.2, C25.2, C26.2, C27.2, C28.2, C29.2, C30.2, C31.2, C32.2, C33.2, C34.2, C35.2, C36.2; also elsewhere on the board
VCC: C1.1, C2.1, C3.1, C4.1, C5.1, C6.1, C7.1, C8.1, C9.1, C10.1, C11.1, C12.1, C13.1, C14.1, C15.1, C16.1, C17.1, C18.1, C19.1, C20.1, C21.1, C22.1, C23.1, C24.1, C25.1, C26.1, C27.1, C28.1, C29.1, C30.1, C31.1, C32.1, C33.1, C34.1, C35.1, C36.1; also elsewhere on the board
